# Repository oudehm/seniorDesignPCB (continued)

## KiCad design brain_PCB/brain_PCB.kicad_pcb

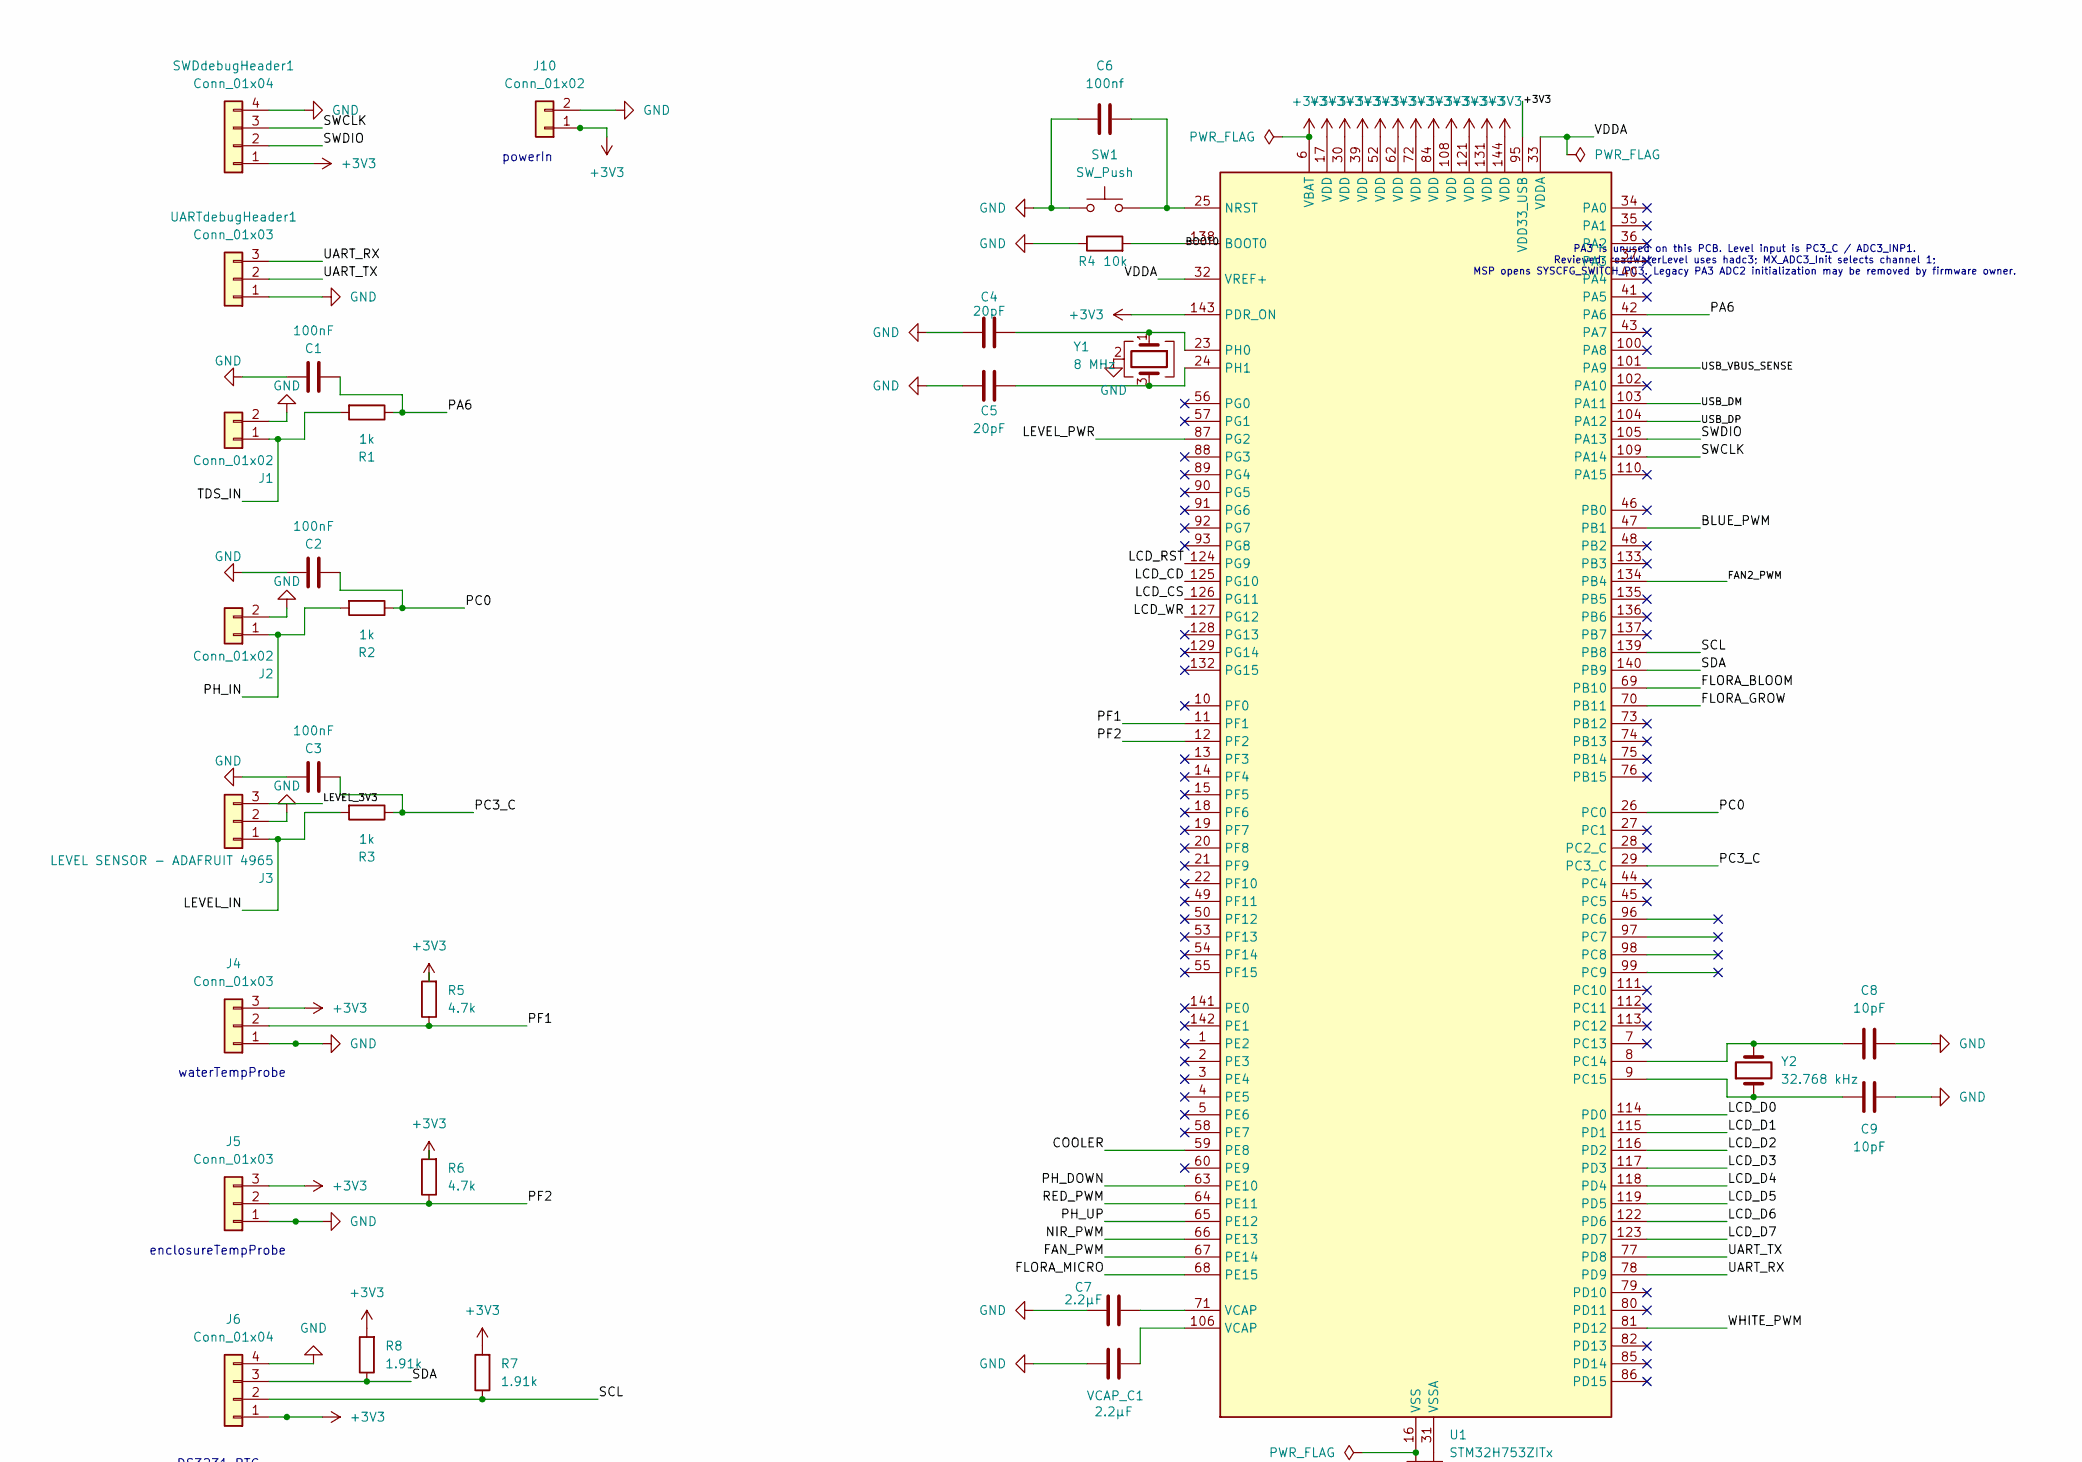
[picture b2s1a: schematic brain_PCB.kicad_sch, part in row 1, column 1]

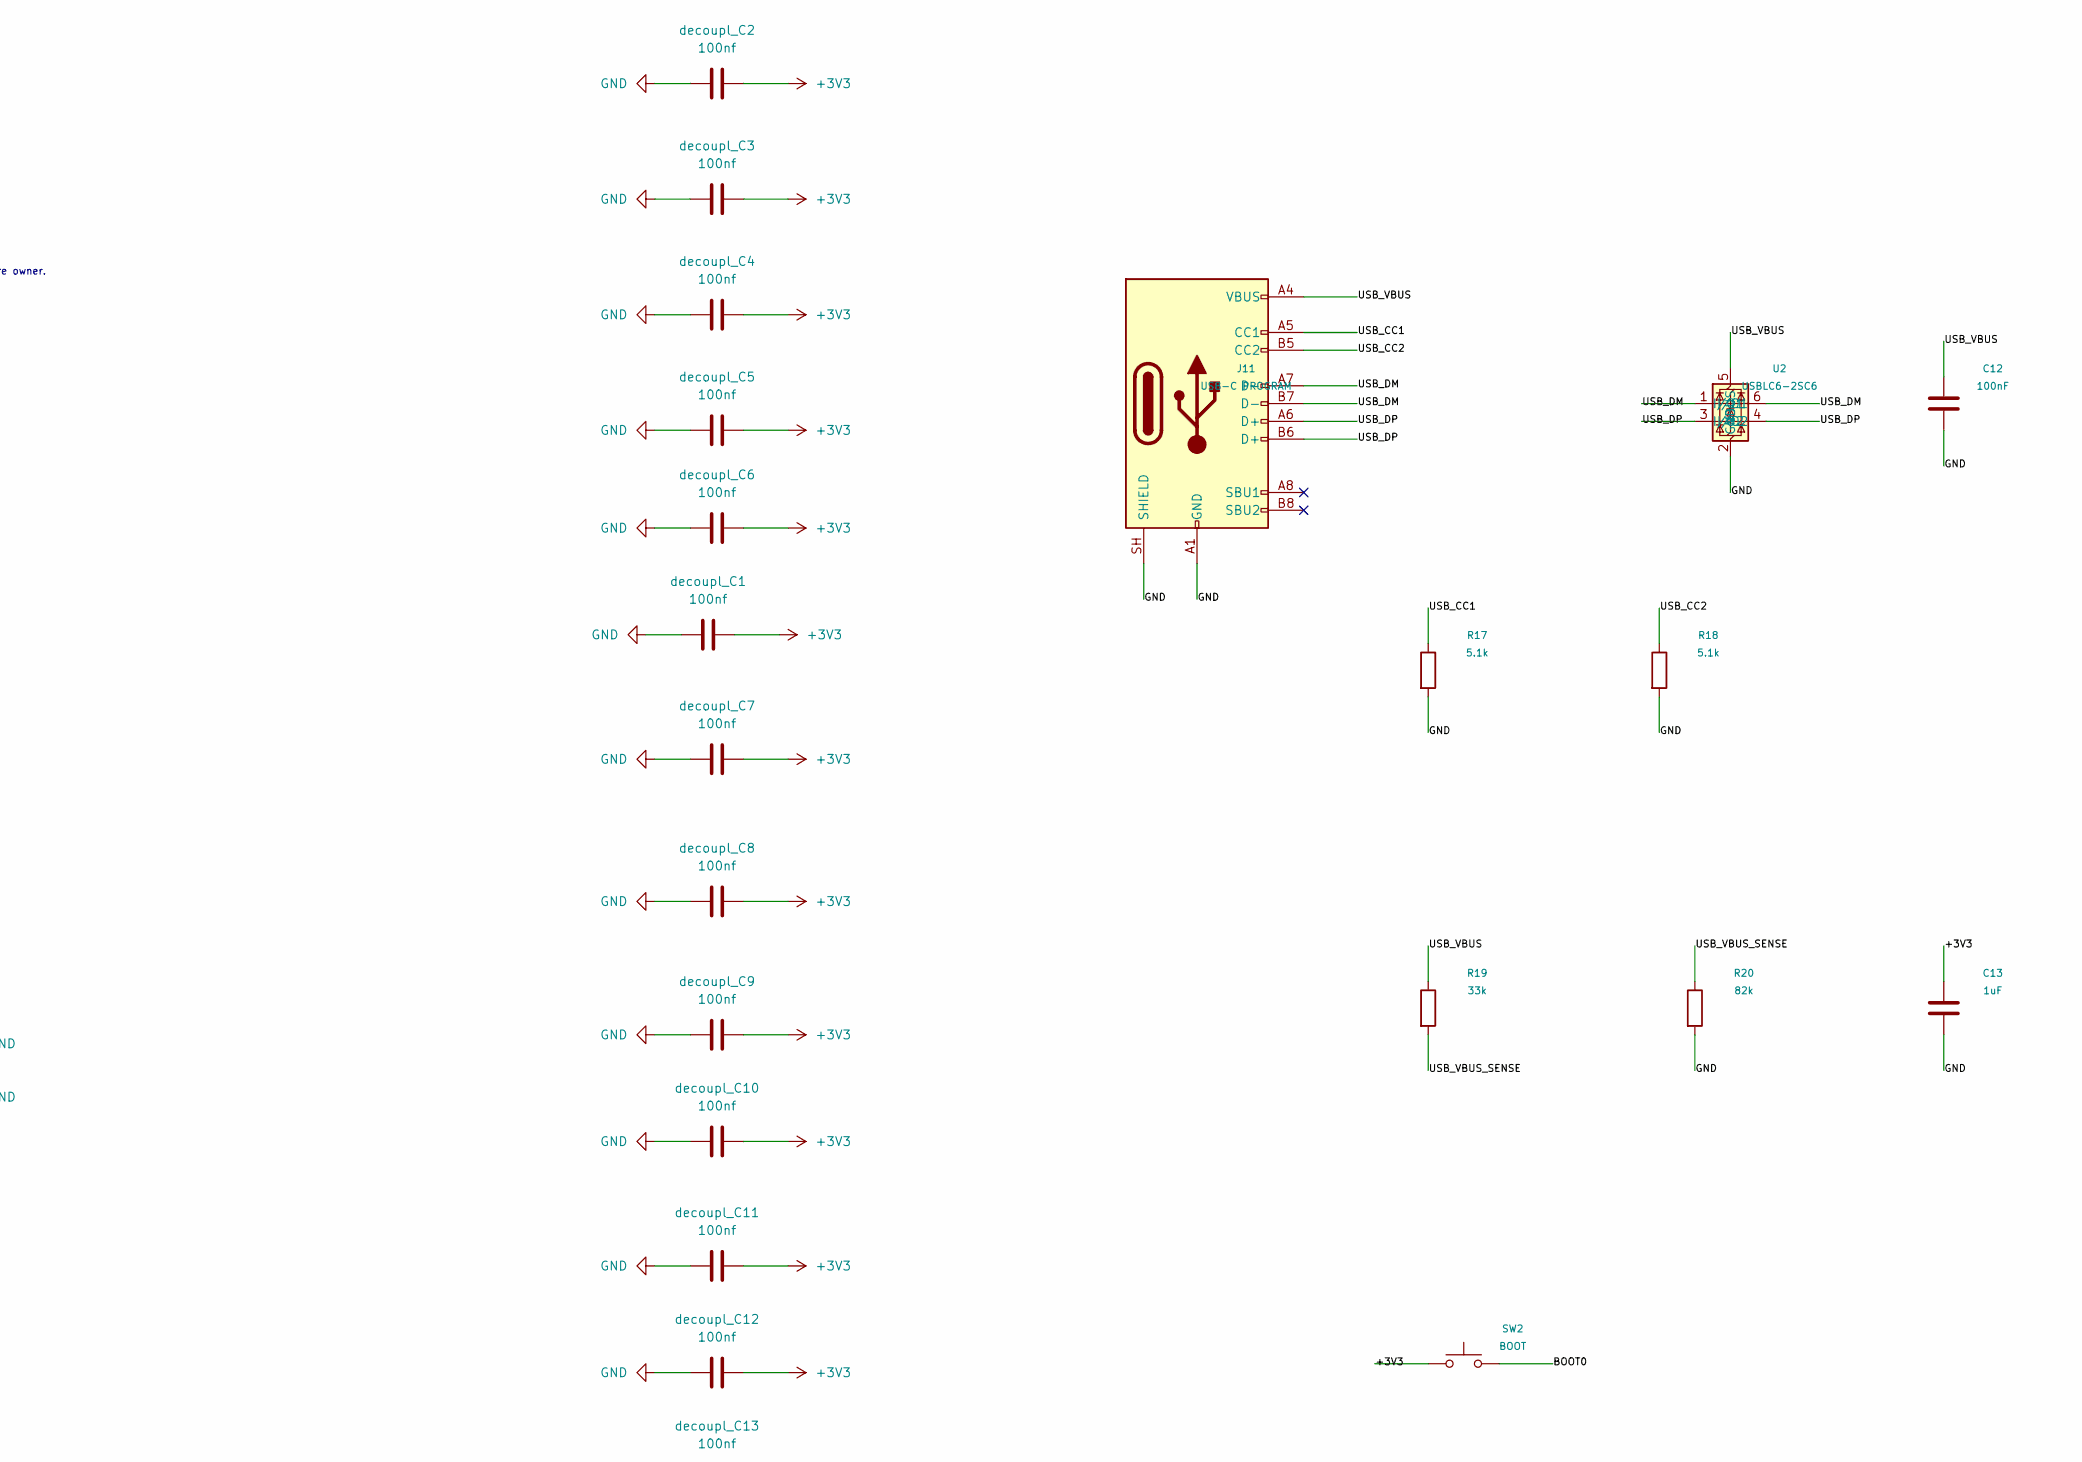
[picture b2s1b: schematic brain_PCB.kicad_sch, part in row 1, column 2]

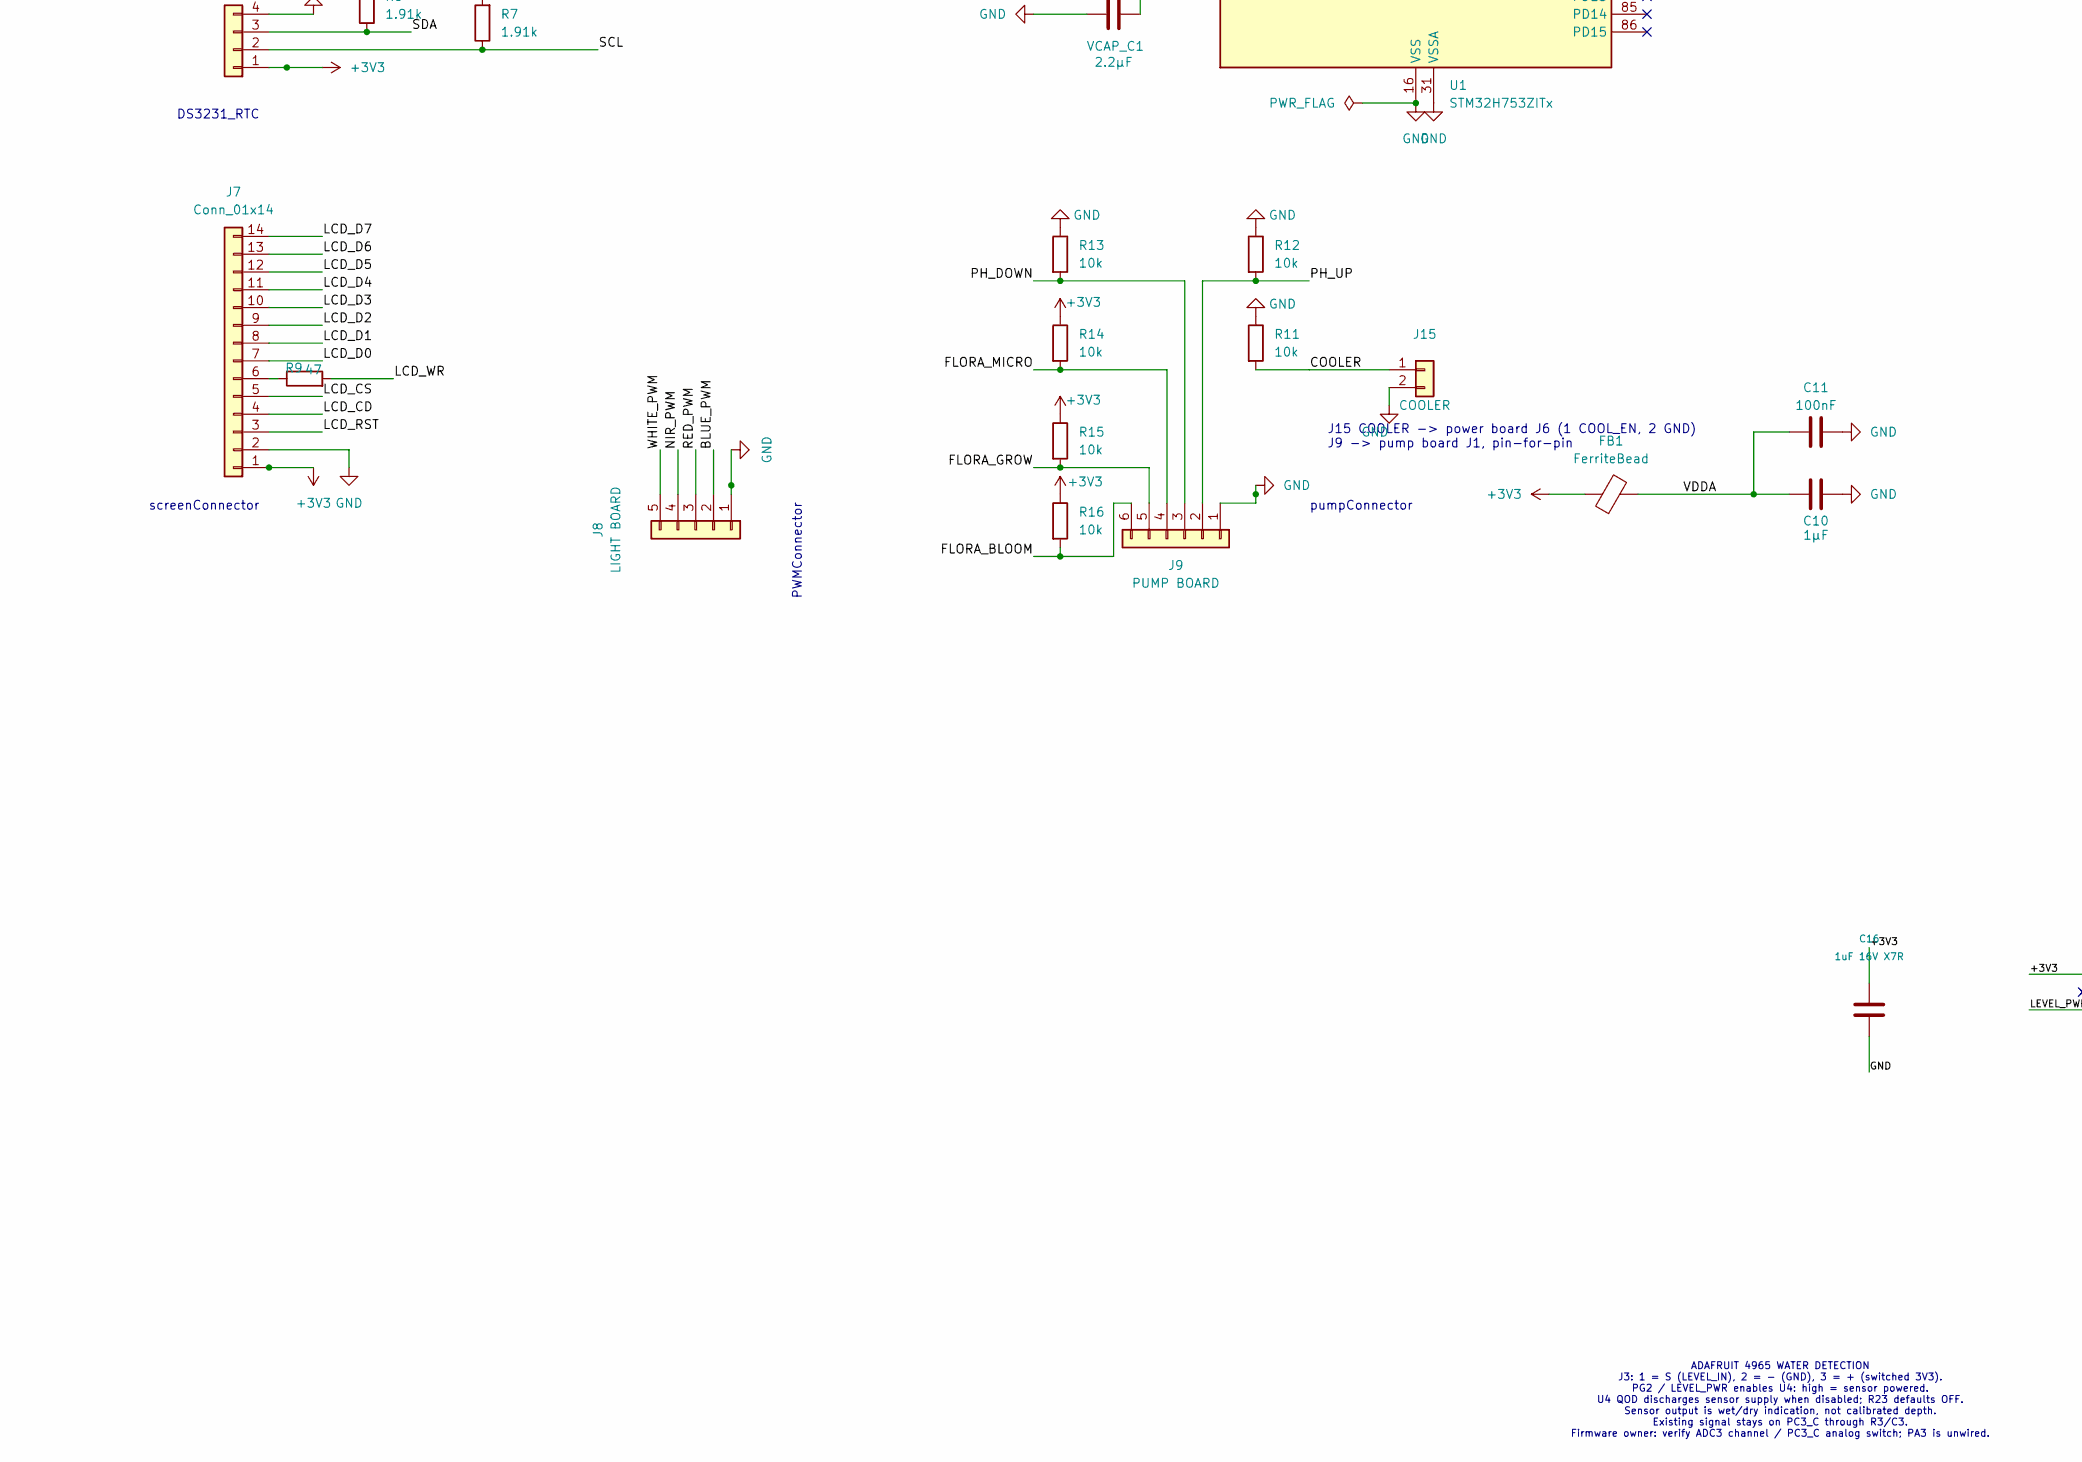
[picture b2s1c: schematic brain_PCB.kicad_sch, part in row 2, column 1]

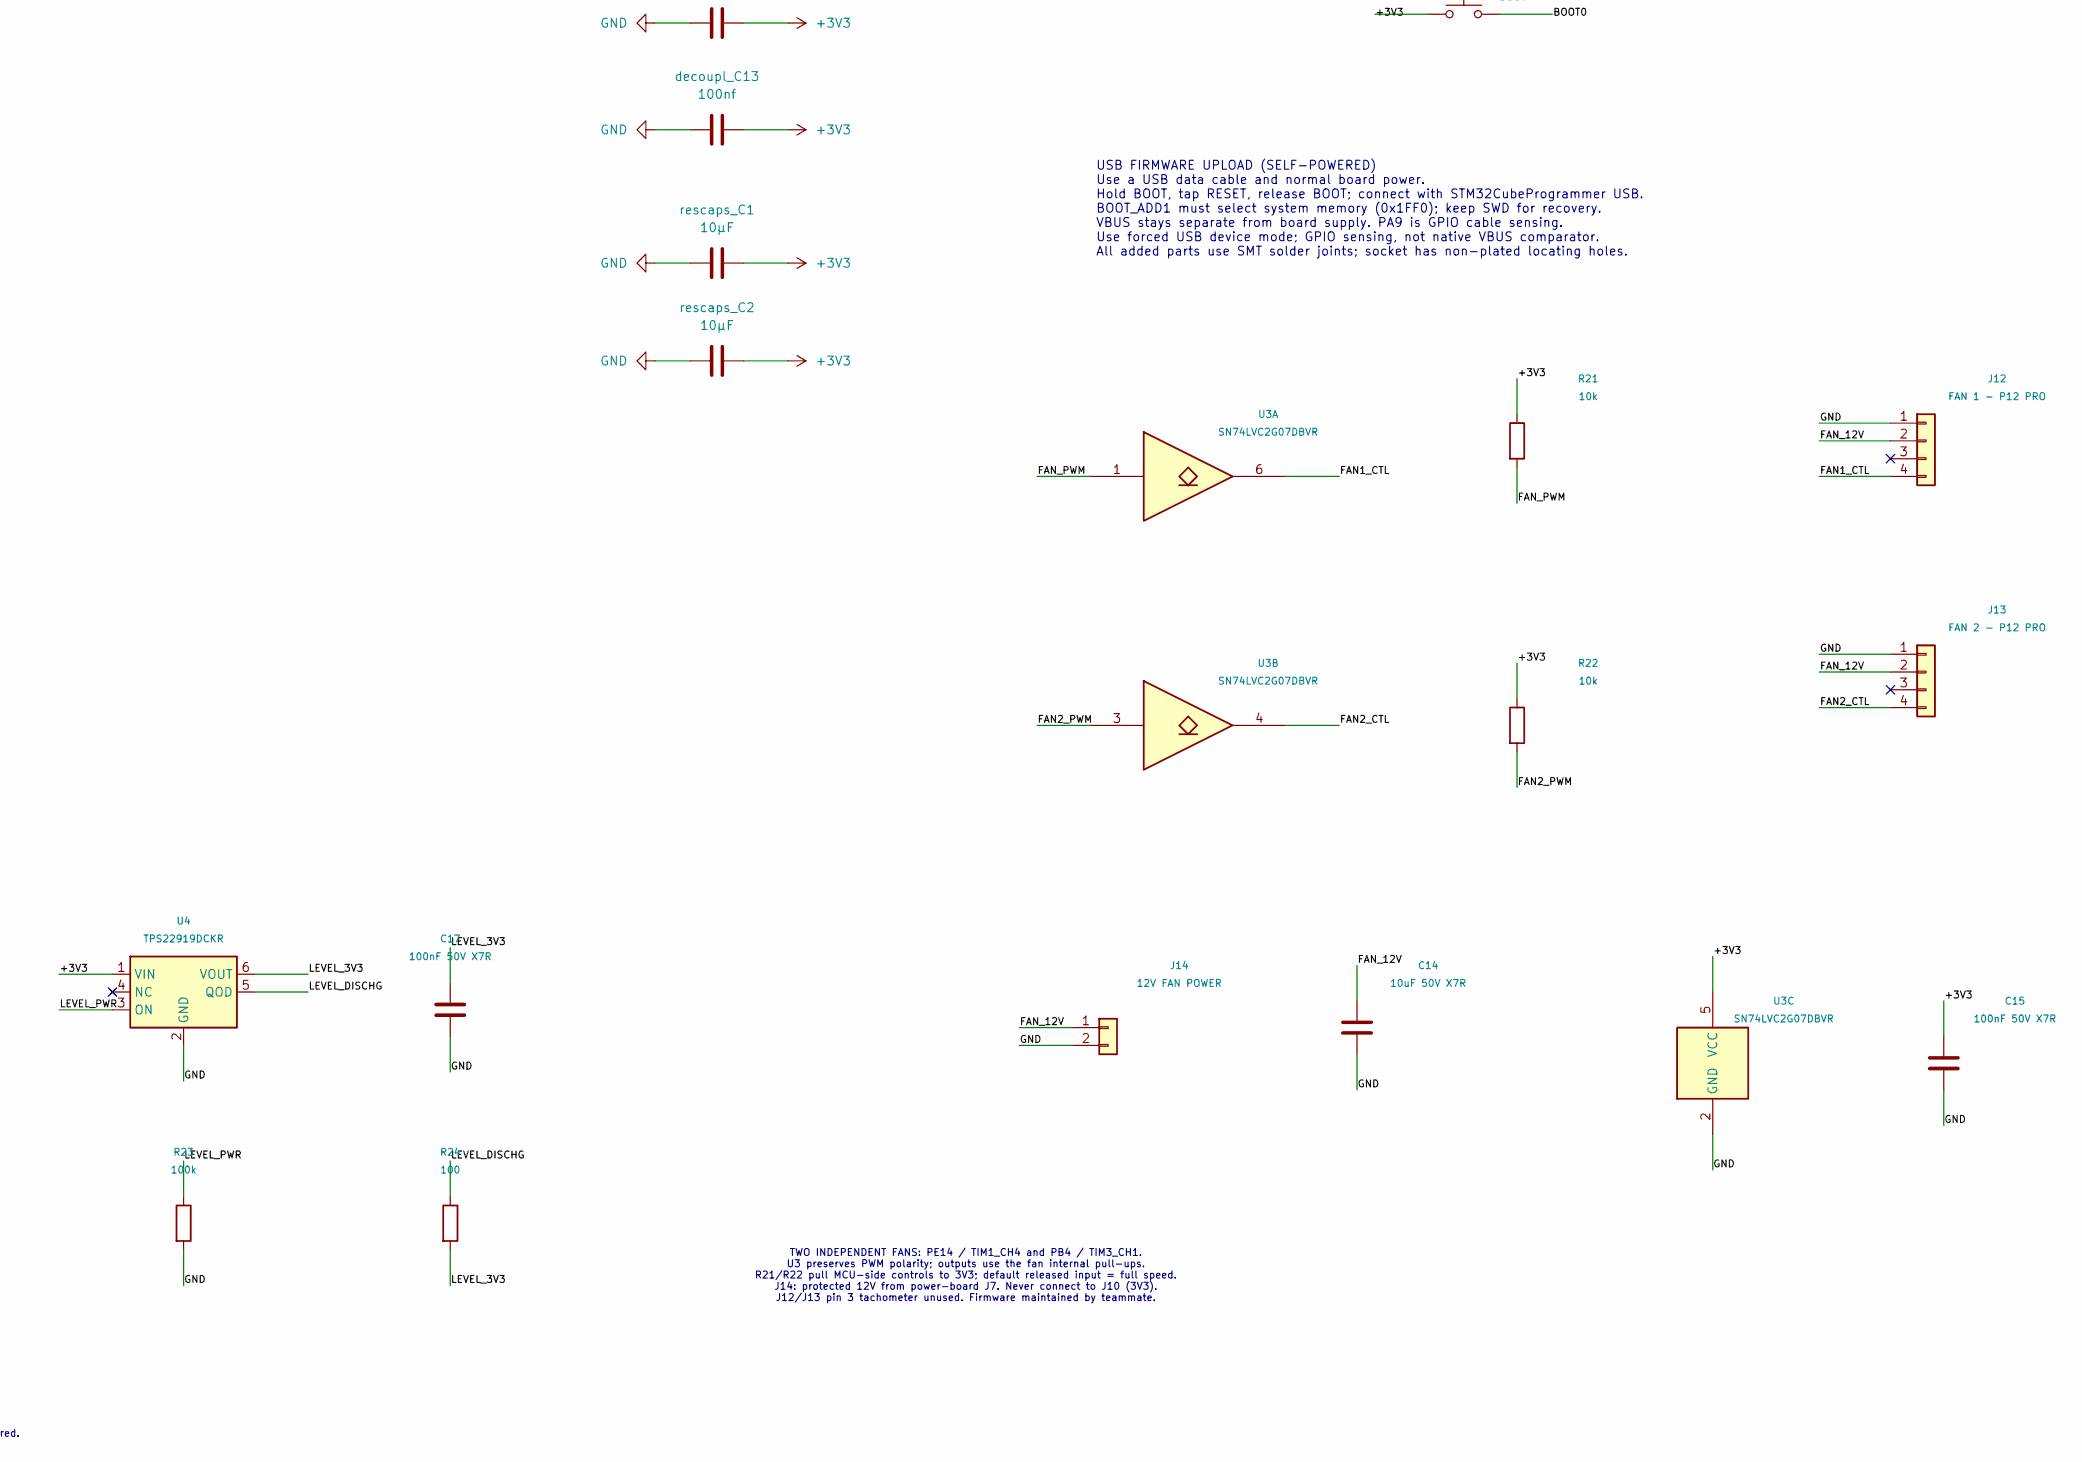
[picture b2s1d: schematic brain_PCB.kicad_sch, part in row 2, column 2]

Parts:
C1: 100nF; C_0402_1005Metric_Reviewed_7; Rating 100nF 50V X7R; MPN GRM155R71H104KE14D; LCSC C77020
C2: 100nF; C_0402_1005Metric_Reviewed_2; Rating 100nF 50V X7R; MPN GRM155R71H104KE14D; LCSC C77020
C3: 100nF; C_0402_1005Metric_Reviewed_10; Rating 100nF 50V X7R; MPN GRM155R71H104KE14D; LCSC C77020
C4: 20pF; C_0402_1005Metric_Reviewed_8; Rating 20pF 50V C0G; MPN GRM1555C1H200JA01D; LCSC C76959
C5: 20pF; C_0402_1005Metric_Reviewed_4; Rating 20pF 50V C0G; MPN GRM1555C1H200JA01D; LCSC C76959
C6: 100nf; C_0402_1005Metric_Reviewed_9; Rating 100nF 50V X7R; MPN GRM155R71H104KE14D; LCSC C77020
C7: 2.2µF; C_0402_1005Metric_Reviewed_6; Rating 2.2uF 10V X5R; MPN GRM155R61A225KE95D; LCSC C77002
C8: 10pF; C_0402_1005Metric_Reviewed_12; Rating 10pF 50V C0G; MPN GRM1555C1H100JA01D; LCSC C76946
C9: 10pF; C_0402_1005Metric_Reviewed_4; Rating 10pF 50V C0G; MPN GRM1555C1H100JA01D; LCSC C76946
C10: 1µF; C_0402_1005Metric_Reviewed_4; Rating 1uF 10V X5R; MPN GRM155R61A105KE15D; LCSC C76999
C11: 100nF; C_0402_1005Metric_Reviewed_4; Rating 100nF 50V X7R; MPN GRM155R71H104KE14D; LCSC C77020
C12: 100nF; C_0402_1005Metric_Reviewed_3; MPN GRM155R71H104KE14D; LCSC C77020
C13: 1uF; C_0402_1005Metric_Reviewed_3; MPN GRM155R61A105KE15D; LCSC C76999
C14: 10uF 50V X7R; C_1210_3225Metric; MPN GRM32ER71H106KA12L; LCSC C77102
C15, C17: 100nF 50V X7R; C_0603_1608Metric; MPN GRM188R71H104KA93D; LCSC C77055
C16: 1uF 16V X7R; C_0603_1608Metric; Rating 1uF 25V X7R 10%, 0603; MPN GRM188R71E105KA12D; LCSC C86020
FB1: FerriteBead; L_0402_1005Metric; Rating 600 ohm at 100MHz; verify analog-rail D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; MPN BLM15AG601SN1D; LCSC C76884
J1, J2, J10: Conn_01x02; JST_XH_B2B-XH-A_1x02_P2.50mm_Vertical; MPN B2B-XH-A(LF)(SN)
J3: LEVEL SENSOR - ADAFRUIT 4965; JST_XH_B3B-XH-A_1x03_P2.50mm_Vertical; MPN B3B-XH-A(LF)(SN)
J4, J5: Conn_01x03; JST_XH_B3B-XH-A_1x03_P2.50mm_Vertical; MPN B3B-XH-A(LF)(SN)
J6: Conn_01x04; JST_XH_B4B-XH-A_1x04_P2.50mm_Vertical; MPN B4B-XH-A(LF)(SN)
J7: Conn_01x14; PinHeader_1x14_P2.54mm_Vertical; MPN 61301411121; LCSC C5907899
J8: LIGHT BOARD; JST_XH_B5B-XH-A_1x05_P2.50mm_Vertical; MPN B5B-XH-A(LF)(SN)
J9: PUMP BOARD; JST_XH_B6B-XH-A_1x06_P2.50mm_Vertical; MPN B6B-XH-A(LF)(SN)
J11: USB-C PROGRAM; USB_C_Receptacle_GCT_USB4110; MPN USB4110-GF-A; LCSC C5143397
J12: FAN 1 - P12 PRO; FanPinHeader_1x04_P2.54mm_Vertical; MPN 470531000; LCSC C240840
J13: FAN 2 - P12 PRO; FanPinHeader_1x04_P2.54mm_Vertical; MPN 470531000; LCSC C240840
J14: 12V FAN POWER; JST_XH_B2B-XH-A_1x02_P2.50mm_Vertical; MPN B2B-XH-A(LF)(SN)
J15: COOLER; JST_XH_B2B-XH-A_1x02_P2.50mm_Vertical; MPN B2B-XH-A(LF)(SN)
R1, R2, R3: 1k; R_0402_1005Metric_Reviewed_2; Rating 1%, 0402, 1/16W; MPN RC0402FR-071KL; LCSC C106235
R4, R11, R12, R13, R14, R15, R16: 10k; R_0402_1005Metric_Reviewed_1; Rating 1%, 0402, 1/16W; MPN RC0402FR-0710KL; LCSC C60490
R5: 4.7k; R_0402_1005Metric_Reviewed_1; Rating 1%, 0402, 1/16W; MPN RC0402FR-074K7L; LCSC C105871
R6: 4.7k; R_0402_1005Metric_Reviewed_6; Rating 1%, 0402, 1/16W; MPN RC0402FR-074K7L; LCSC C105871
R7, R8: 1.91k; R_0402_1005Metric_Reviewed_2; Rating 1.91kohm, 1%, 0402, 62.5mW; MPN RC0402FR-071K91L; LCSC C477598
R9: 47; R_0402_1005Metric_Reviewed_3; Rating 1%, 0402, 1/16W; MPN RC0402FR-0747RL; LCSC C137973
R17, R18: 5.1k; R_0402_1005Metric_Reviewed_5; MPN RC0402FR-075K1L; LCSC C105872
R19: 33k; R_0402_1005Metric_Reviewed_6; MPN RC0402FR-0733KL; LCSC C138003
R20: 82k; R_0402_1005Metric_Reviewed_4; MPN RC0402FR-0782KL; LCSC C137932
R21, R22: 10k; R_0603_1608Metric; MPN RC0603FR-0710KL; LCSC C98220
R23: 100k; R_0603_1608Metric; MPN RC0603FR-07100KL; LCSC C14675
R24: 100; R_0603_1608Metric; MPN RC0603FR-07100RL; LCSC C105588
SW1: SW_Push; SW_SPST_PTS645Sx43SMTR92; Rating SMT push switch; MPN PTS645SM43SMTR92 LFS; LCSC C221880
SW2: BOOT; SW_SPST_PTS645Sx43SMTR92; MPN PTS645SM43SMTR92 LFS; LCSC C221880
SWDdebugHeader1: Conn_01x04; PinHeader_1x04_P2.54mm_Vertical; MPN 61300411121; LCSC C5184785
U1: STM32H753ZITx; LQFP-144_20x20mm_P0.5mm; Rating LQFP144, -40 to 85C; MPN STM32H753ZIT6; LCSC C730207
U2: USBLC6-2SC6; SOT-23-6; MPN USBLC6-2SC6; LCSC C7519
U3: SN74LVC2G07DBVR; SOT-23-6; MPN SN74LVC2G07DBVR; LCSC C37708
U4: TPS22919DCKR; SOT-363_SC-70-6; MPN TPS22919DCKR; LCSC C2149796
UARTdebugHeader1: Conn_01x03; PinHeader_1x03_P2.54mm_Vertical; MPN 61300311121; LCSC C2915006
VCAP_C1: 2.2µF; C_0402_1005Metric_Reviewed_1; Rating 2.2uF 10V X5R; MPN GRM155R61A225KE95D; LCSC C77002
Y1: 8 MHz; Crystal_SMD_3225-4Pin_3.2x2.5mm_Reviewed_1; Rating 8MHz, CL=12pF, ESR max 400 ohm; MPN ECS-80-12-33-JGN-TR; LCSC C2442665
Y2: 32.768 kHz; Crystal_SMD_3215-2Pin_3.2x1.5mm_Reviewed_1; Rating 32.768kHz, CL=7pF; MPN ABS07-32.768KHZ-7-T; LCSC C276424
decoupl_C1, decoupl_C2, decoupl_C3: 100nf; C_0402_1005Metric_Reviewed_7; Rating 100nF 50V X7R; MPN GRM155R71H104KE14D; LCSC C77020
decoupl_C4, decoupl_C5, decoupl_C7: 100nf; C_0402_1005Metric_Reviewed_6; Rating 100nF 50V X7R; MPN GRM155R71H104KE14D; LCSC C77020
decoupl_C6: 100nf; C_0402_1005Metric_Reviewed_11; Rating 100nF 50V X7R; MPN GRM155R71H104KE14D; LCSC C77020
decoupl_C8, decoupl_C9, decoupl_C10: 100nf; C_0402_1005Metric_Reviewed_1; Rating 100nF 50V X7R; MPN GRM155R71H104KE14D; LCSC C77020
decoupl_C11, decoupl_C12: 100nf; C_0402_1005Metric_Reviewed_13; Rating 100nF 50V X7R; MPN GRM155R71H104KE14D; LCSC C77020
decoupl_C13: 100nf; C_0402_1005Metric_Reviewed_5; Rating 100nF 50V X7R; MPN GRM155R71H104KE14D; LCSC C77020
rescaps_C1, rescaps_C2: 10µF; C_0402_1005Metric_Reviewed_7; Rating 10uF 6.3V X5R; MPN GRM155R60J106ME15D; LCSC C412251

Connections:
+3V3: C13.1, C15.1, C16.1, FB1.1, J4.3, J5.3, J6.1, J7.1, J10.1, R5.2, R6.2, R7.2, R8.2, R14.1, R15.1, R16.1, R21.1, R22.1, SW2.1, SWDdebugHeader1.1, U1.6 (VBAT), U1.17 (VDD), U1.30 (VDD), U1.39 (VDD), U1.52 (VDD), U1.62 (VDD), U1.72 (VDD), U1.84 (VDD), U1.95 (VDD33_USB), U1.108 (VDD), U1.121 (VDD), U1.131 (VDD), U1.143 (PDR_ON), U1.144 (VDD), U3.5 (VCC), U4.1 (VIN), decoupl_C1.2, decoupl_C2.2, decoupl_C3.2, decoupl_C4.2, decoupl_C5.2, decoupl_C6.2, decoupl_C7.2, decoupl_C8.2, decoupl_C9.2, decoupl_C10.2, decoupl_C11.2, decoupl_C12.2, decoupl_C13.2, rescaps_C1.2, rescaps_C2.2
/BLUE_PWM: J8.2, U1.47 (PB1)
/BOOT0: R4.2, SW2.2, U1.138 (BOOT0)
/COOLER: J15.1, R11.2, U1.59 (PE8)
/FAN1_CTL: J12.4, U3.6
/FAN2_CTL: J13.4, U3.4
/FAN2_PWM: R22.2, U1.134 (PB4), U3.3
/FAN_12V: C14.1, J12.2, J13.2, J14.1
/FAN_PWM: R21.2, U1.67 (PE14), U3.1
/FLORA_BLOOM: J9.6, R16.2, U1.69 (PB10)
/FLORA_GROW: J9.5, R15.2, U1.70 (PB11)
/FLORA_MICRO: J9.4, R14.2, U1.68 (PE15)
/LCD_CD: J7.4, U1.125 (PG10)
/LCD_CS: J7.5, U1.126 (PG11)
/LCD_D0: J7.7, U1.114 (PD0)
/LCD_D1: J7.8, U1.115 (PD1)
/LCD_D2: J7.9, U1.116 (PD2)
/LCD_D3: J7.10, U1.117 (PD3)
/LCD_D4: J7.11, U1.118 (PD4)
/LCD_D5: J7.12, U1.119 (PD5)
/LCD_D6: J7.13, U1.122 (PD6)
/LCD_D7: J7.14, U1.123 (PD7)
/LCD_RST: J7.3, U1.124 (PG9)
/LCD_WR: R9.2, U1.127 (PG12)
/LEVEL_3V3: C17.1, J3.3, R24.2, U4.6 (VOUT)
/LEVEL_DISCHG: R24.1, U4.5 (QOD)
/LEVEL_IN: J3.1, R3.2
/LEVEL_PWR: R23.1, U1.87 (PG2), U4.3 (ON)
/NIR_PWM: J8.4, U1.66 (PE13)
/PA6: C1.1, R1.1, U1.42 (PA6)
/PC0: C2.1, R2.1, U1.26 (PC0)
/PC3_C: C3.1, R3.1, U1.29 (PC3_C)
/PF1: J4.2, R5.1, U1.11 (PF1)
/PF2: J5.2, R6.1, U1.12 (PF2)
/PH_DOWN: J9.3, R13.2, U1.63 (PE10)
/PH_IN: J2.1, R2.2
/PH_UP: J9.2, R12.2, U1.65 (PE12)
/RED_PWM: J8.3, U1.64 (PE11)
/SCL: J6.2, R7.1, U1.139 (PB8)
/SDA: J6.3, R8.1, U1.140 (PB9)
/SWCLK: SWDdebugHeader1.3, U1.109 (PA14)
/SWDIO: SWDdebugHeader1.2, U1.105 (PA13)
/TDS_IN: J1.1, R1.2
/UART_RX: U1.78 (PD9), UARTdebugHeader1.3
/UART_TX: U1.77 (PD8), UARTdebugHeader1.2
/USB_CC1: J11.A5 (CC1), R17.1
/USB_CC2: J11.B5 (CC2), R18.1
/USB_DM: J11.A7 (D-), J11.B7 (D-), U1.103 (PA11), U2.1 (I/O1), U2.6 (I/O1)
/USB_DP: J11.A6 (D+), J11.B6 (D+), U1.104 (PA12), U2.3 (I/O2), U2.4 (I/O2)
/USB_VBUS: C12.1, J11.A4 (VBUS), J11.A9 (VBUS), J11.B4 (VBUS), J11.B9 (VBUS), R19.1, U2.5 (VBUS)
/USB_VBUS_SENSE: R19.2, R20.1, U1.101 (PA9)
/VDDA: C10.1, C11.1, FB1.2, U1.32 (VREF+), U1.33 (VDDA)
/WHITE_PWM: J8.5, U1.81 (PD12)
GND: C1.2, C2.2, C3.2, C4.1, C5.2, C6.1, C7.1, C8.1, C9.2, C10.2, C11.2, C12.2, C13.2, C14.2, C15.2, C16.2, C17.2, J1.2, J2.2, J3.2, J4.1, J5.1, J6.4, J7.2, J8.1, J9.1, J10.2, J11.A1 (GND), J11.A12 (GND), J11.B1 (GND), J11.B12 (GND), J11.SH (SHIELD), J12.1, J13.1, J14.2, J15.2, R4.1, R11.1, R12.1, R13.1, R17.2, R18.2, R20.2, R23.2, SW1.1, SWDdebugHeader1.4, U1.16 (VSS), U1.31 (VSSA), U1.38 (VSS), U1.51 (VSS), U1.61 (VSS), U1.83 (VSS), U1.94 (VSS), U1.107 (VSS), U1.120 (VSS), U1.130 (VSS), U2.2 (GND), U3.2 (GND), U4.2 (GND), UARTdebugHeader1.1, VCAP_C1.1, Y1.2, Y1.4 (G), decoupl_C1.1, decoupl_C2.1, decoupl_C3.1, decoupl_C4.1, decoupl_C5.1, decoupl_C6.1, decoupl_C7.1, decoupl_C8.1, decoupl_C9.1, decoupl_C10.1, decoupl_C11.1, decoupl_C12.1, decoupl_C13.1, rescaps_C1.1, rescaps_C2.1
unnamed: C7.2, U1.71 (VCAP)
unnamed: J7.6, R9.1
unnamed: C6.2, SW1.2, U1.25 (NRST)
unnamed: C8.2, U1.8 (PC14), Y2.2
unnamed: C9.1, U1.9 (PC15), Y2.1
unnamed: C4.2, U1.23 (PH0), Y1.1
unnamed: C5.1, U1.24 (PH1), Y1.3
unnamed: U1.106 (VCAP), VCAP_C1.2

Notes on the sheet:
DS3231_RTC
PWMConnector
powerIn
enclosureTempProbe
waterTempProbe
screenConnector
pumpConnector
J15 COOLER -> power board J6 (1 COOL_EN, 2 GND) J9 -> pump board J1, pin-for-pin
USB FIRMWARE UPLOAD (SELF-POWERED) Use a USB data cable and normal board power. Hold BOOT, tap RESET, release BOOT; connect with STM32CubeProgrammer USB. BOOT_ADD1 must select system memory (0x1FF0); keep SWD for recovery. VBUS stays separate from board supply. PA9 is GPIO cable sensing. Use forced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
TWO INDEPENDENT FANS: PE14 / TIM1_CH4 and PB4 / TIM3_CH1. U3 preserves PWM polarity; outputs use the fan internal pull-ups. R21/R22 pull MCU-side controls to 3V3; default released input = full speed. J14: protected 12V from power-board J7. Never connect to J10 (3V3). J12/J13 pin 3 tachometer unused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
ADAFRUIT 4965 WATER DETECTION J3: 1 = S (LEVEL_IN), 2 = - (GND), 3 = + (switched 3V3). PG2 / LEVEL_PWR enables U4: high = sensor powered. U4 QOD discharges sensor supply when disabled; R23 defaults OFF. Sensor output is wet/dry indication, not calibrated depth. Existing signal stays on PC3_C throug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
PA3 is unused on this PCB. Level input is PC3_C / ADC3_INP1. Reviewed: readWaterLevel uses hadc3; MX_ADC3_Init selects channel 1; MSP opens SYSCFG_SWITCH_PC3. Legacy PA3 ADC2 initialization may be removed by firmware owner.

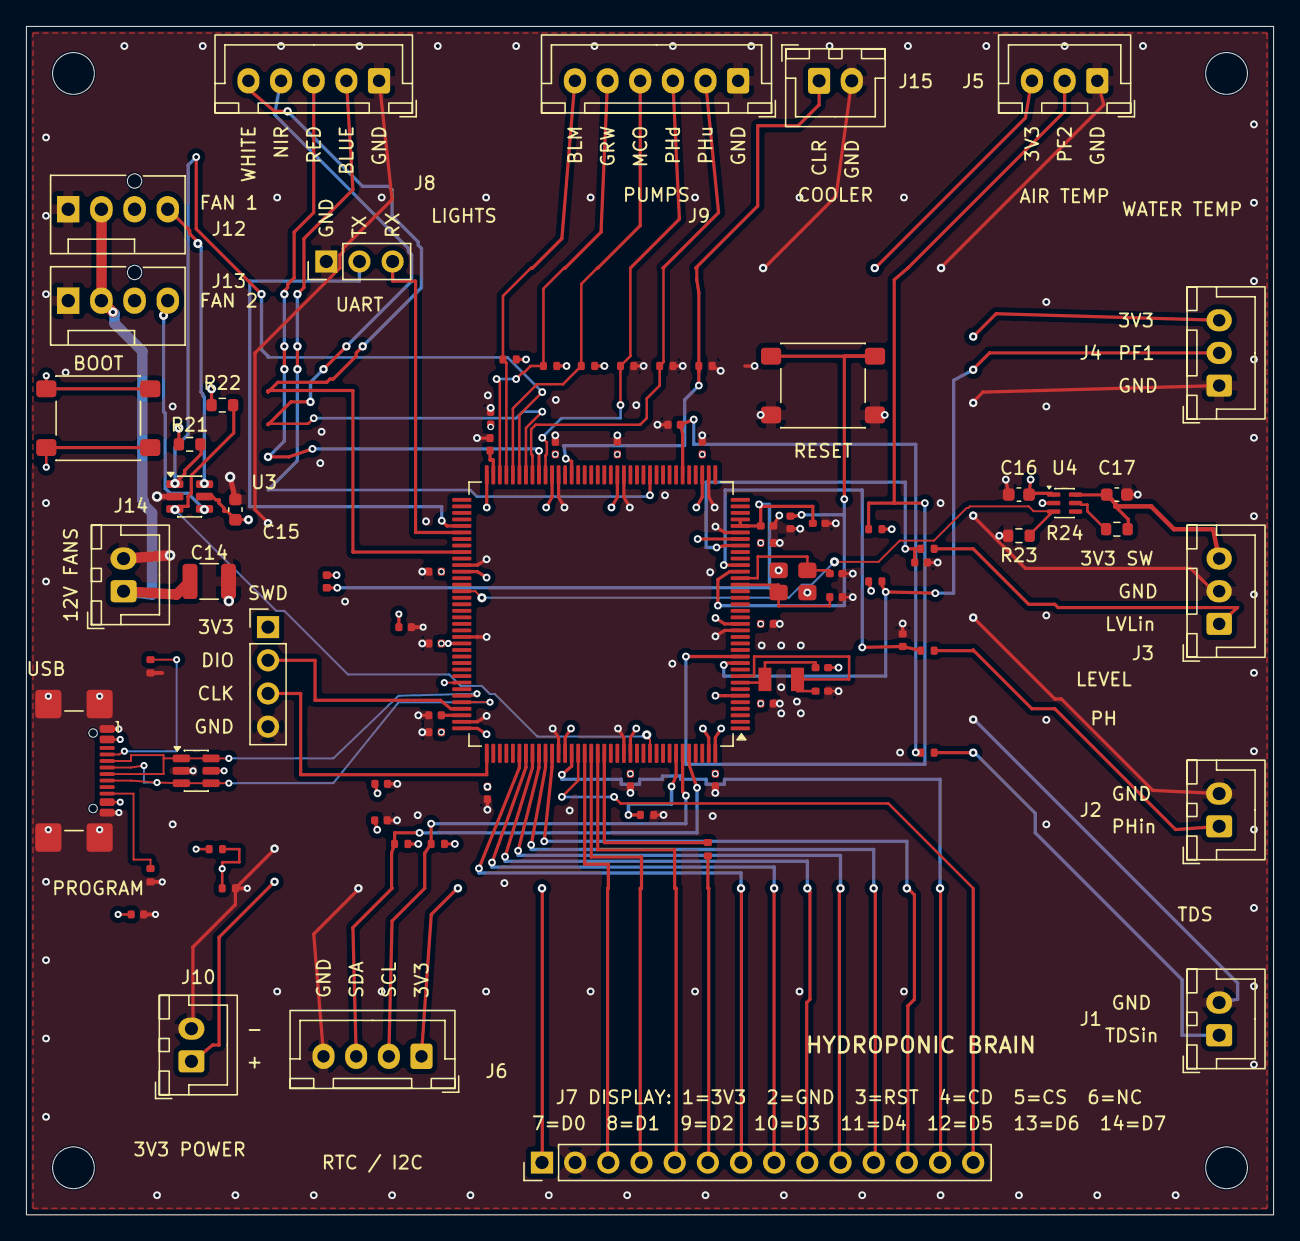
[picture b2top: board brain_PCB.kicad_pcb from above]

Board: 4 copper layers, 95.5 x 91.0 mm, 86 parts (0 on the bottom side), 62 nets.

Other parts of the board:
H1, H2, H3, H4: MountingHole_3.2mm_M3
